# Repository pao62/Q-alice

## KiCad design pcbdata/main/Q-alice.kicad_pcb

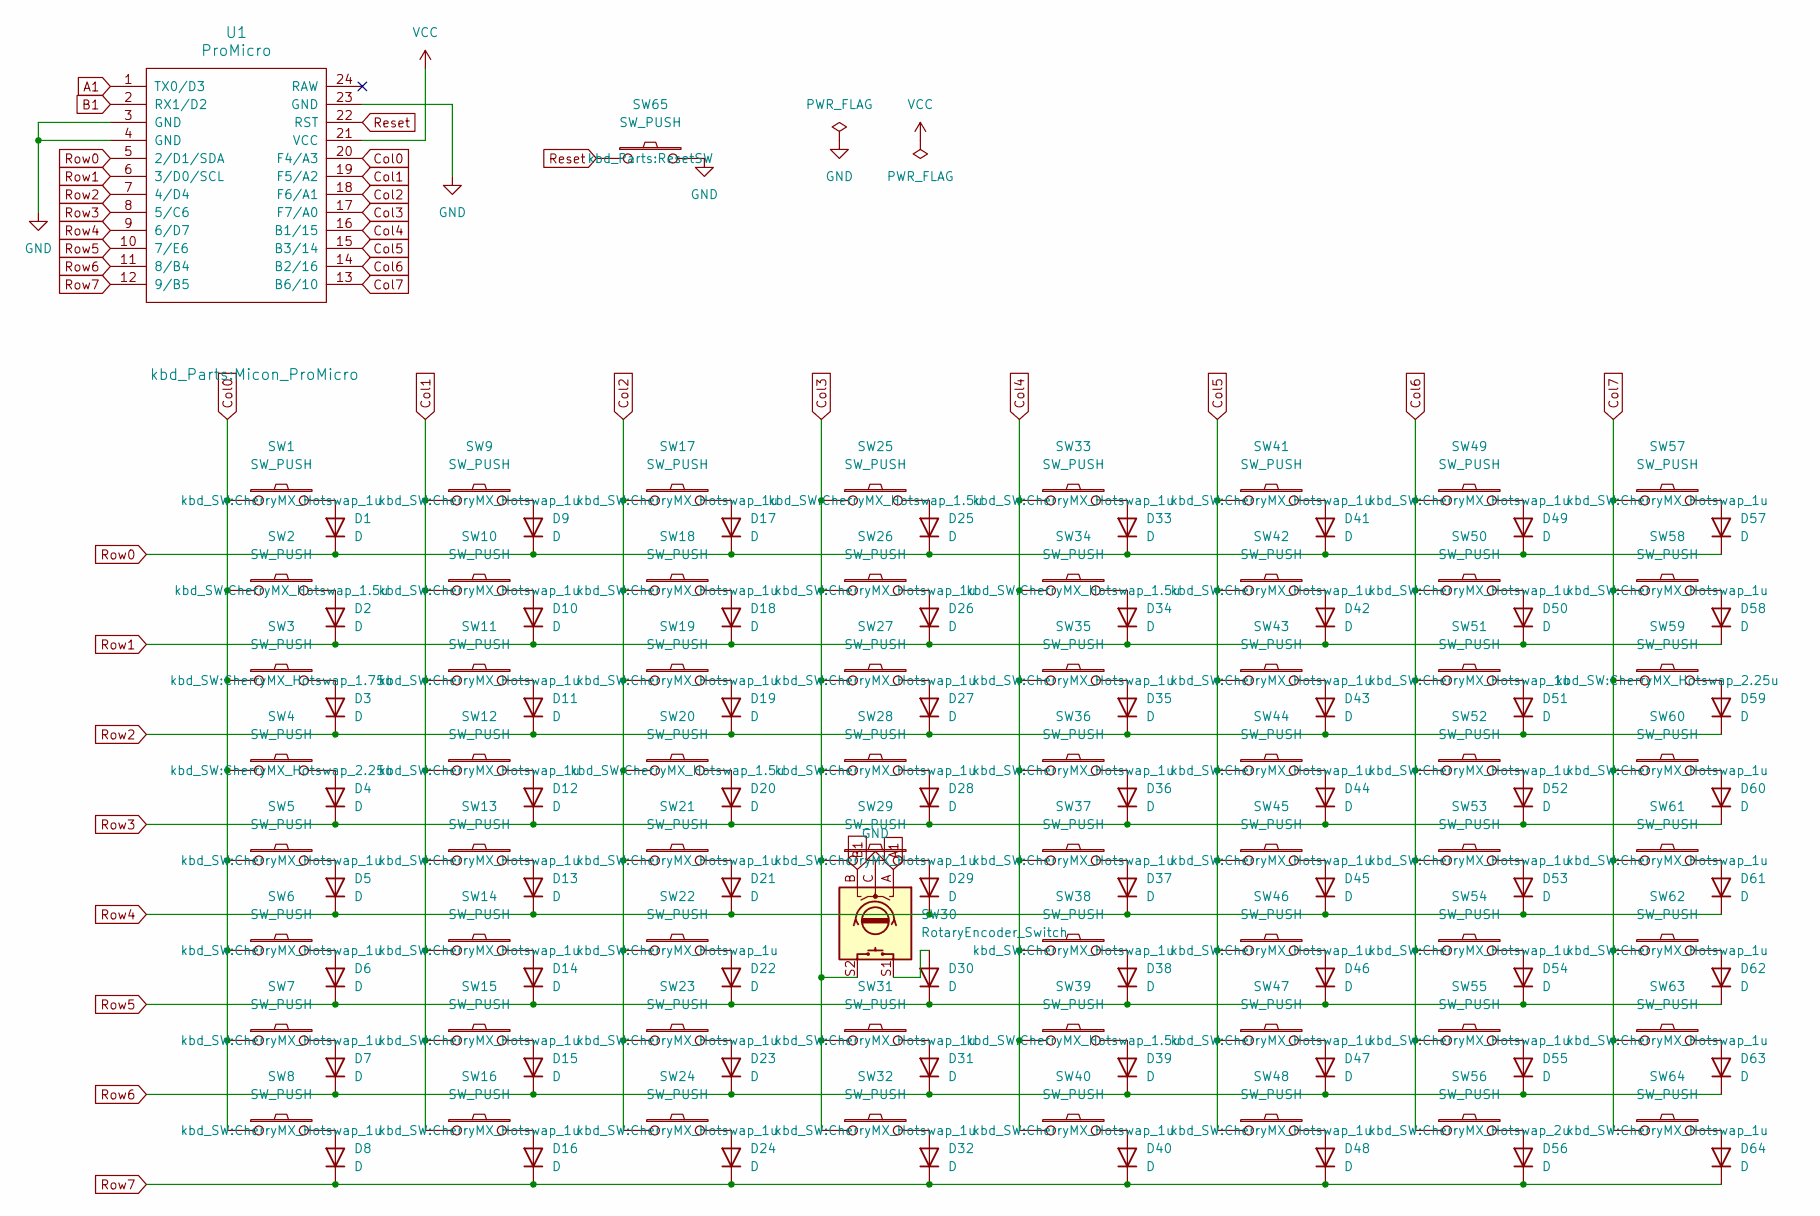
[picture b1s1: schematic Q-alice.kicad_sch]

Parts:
D1, D2, D3, D4, D5, D6, D7, D8, D9, D10, D11, D12, D13, D14, D15, D16, D17, D18, D19, D20, D21, D22, D23, D24, D25, D26, D27, D28, D29, D30, D31, D32, D33, D34, D35, D36, D37, D38, D39, D40, D41, D42, D43, D44, D45, D46, D47, D48, D49, D50, D51, D52, D53, D54, D55, D56, D57, D58, D59, D60, D61, D62, D63, D64: D; Diode_SMD
SW1, SW5, SW6, SW7, SW8, SW9, SW10, SW11, SW12, SW13, SW14, SW15, SW16, SW17, SW18, SW19, SW21, SW22, SW23, SW24, SW26, SW27, SW28, SW29, SW31, SW32, SW33, SW35, SW36, SW37, SW38, SW40, SW41, SW42, SW43, SW44, SW45, SW46, SW47, SW48, SW49, SW50, SW51, SW52, SW53, SW54, SW55, SW57, SW58, SW60, SW61, SW62, SW63, SW64: SW_PUSH; CherryMX_Hotswap_1u
SW2, SW20, SW25, SW34, SW39: SW_PUSH; CherryMX_Hotswap_1.5u
SW3: SW_PUSH; CherryMX_Hotswap_1.75u
SW4, SW59: SW_PUSH; CherryMX_Hotswap_2.25u
SW30: RotaryEncoder_Switch; RotaryEncoder_EC12E
SW56: SW_PUSH; CherryMX_Hotswap_2u
SW65: SW_PUSH; ResetSW
U1: ProMicro; Micon_ProMicro

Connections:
A1: SW30.A, U1.1 (TX0/D3)
B1: SW30.B, U1.2 (RX1/D2)
Col0: SW1.1, SW2.1, SW3.1, SW4.1, SW5.1, SW6.1, SW7.1, SW8.1, U1.20 (F4/A3)
Col1: SW9.1, SW10.1, SW11.1, SW12.1, SW13.1, SW14.1, SW15.1, SW16.1, U1.19 (F5/A2)
Col2: SW17.1, SW18.1, SW19.1, SW20.1, SW21.1, SW22.1, SW23.1, SW24.1, U1.18 (F6/A1)
Col3: SW25.1, SW26.1, SW27.1, SW28.1, SW29.1, SW30.S2, SW31.1, SW32.1, U1.17 (F7/A0)
Col4: SW33.1, SW34.1, SW35.1, SW36.1, SW37.1, SW38.1, SW39.1, SW40.1, U1.16 (B1/15)
Col5: SW41.1, SW42.1, SW43.1, SW44.1, SW45.1, SW46.1, SW47.1, SW48.1, U1.15 (B3/14)
Col6: SW49.1, SW50.1, SW51.1, SW52.1, SW53.1, SW54.1, SW55.1, SW56.1, U1.14 (B2/16)
Col7: SW57.1, SW58.1, SW59.1, SW60.1, SW61.1, SW62.1, SW63.1, SW64.1, U1.13 (B6/10)
GND: SW30.C, SW65.2, U1.3 (GND), U1.4 (GND), U1.23 (GND)
unnamed: D1.2 (A), SW1.2
unnamed: D2.2 (A), SW2.2
unnamed: D3.2 (A), SW3.2
unnamed: D4.2 (A), SW4.2
unnamed: D5.2 (A), SW5.2
unnamed: D6.2 (A), SW6.2
unnamed: D7.2 (A), SW7.2
unnamed: D8.2 (A), SW8.2
unnamed: D9.2 (A), SW9.2
unnamed: D10.2 (A), SW10.2
unnamed: D11.2 (A), SW11.2
unnamed: D12.2 (A), SW12.2
unnamed: D13.2 (A), SW13.2
unnamed: D14.2 (A), SW14.2
unnamed: D15.2 (A), SW15.2
unnamed: D16.2 (A), SW16.2
unnamed: D17.2 (A), SW17.2
unnamed: D18.2 (A), SW18.2
unnamed: D19.2 (A), SW19.2
unnamed: D20.2 (A), SW20.2
unnamed: D21.2 (A), SW21.2
unnamed: D22.2 (A), SW22.2
unnamed: D23.2 (A), SW23.2
unnamed: D24.2 (A), SW24.2
unnamed: D25.2 (A), SW25.2
unnamed: D26.2 (A), SW26.2
unnamed: D27.2 (A), SW27.2
unnamed: D28.2 (A), SW28.2
unnamed: D29.2 (A), SW29.2
unnamed: D30.2 (A), SW30.S1
unnamed: D31.2 (A), SW31.2
unnamed: D32.2 (A), SW32.2
unnamed: D33.2 (A), SW33.2
unnamed: D34.2 (A), SW34.2
unnamed: D35.2 (A), SW35.2
unnamed: D36.2 (A), SW36.2
unnamed: D37.2 (A), SW37.2
unnamed: D38.2 (A), SW38.2
unnamed: D39.2 (A), SW39.2
unnamed: D40.2 (A), SW40.2
unnamed: D41.2 (A), SW41.2
unnamed: D42.2 (A), SW42.2
unnamed: D43.2 (A), SW43.2
unnamed: D44.2 (A), SW44.2
unnamed: D45.2 (A), SW45.2
unnamed: D46.2 (A), SW46.2
unnamed: D47.2 (A), SW47.2
unnamed: D48.2 (A), SW48.2
unnamed: D49.2 (A), SW49.2
unnamed: D50.2 (A), SW50.2
unnamed: D51.2 (A), SW51.2
unnamed: D52.2 (A), SW52.2
unnamed: D53.2 (A), SW53.2
unnamed: D54.2 (A), SW54.2
unnamed: D55.2 (A), SW55.2
unnamed: D56.2 (A), SW56.2
unnamed: D57.2 (A), SW57.2
unnamed: D58.2 (A), SW58.2
unnamed: D59.2 (A), SW59.2
unnamed: D60.2 (A), SW60.2
unnamed: D61.2 (A), SW61.2
unnamed: D62.2 (A), SW62.2
unnamed: D63.2 (A), SW63.2
unnamed: D64.2 (A), SW64.2
Reset: SW65.1, U1.22 (RST)
Row0: D1.1 (K), D9.1 (K), D17.1 (K), D25.1 (K), D33.1 (K), D41.1 (K), D49.1 (K), D57.1 (K), U1.5 (2/D1/SDA)
Row1: D2.1 (K), D10.1 (K), D18.1 (K), D26.1 (K), D34.1 (K), D42.1 (K), D50.1 (K), D58.1 (K), U1.6 (3/D0/SCL)
Row2: D3.1 (K), D11.1 (K), D19.1 (K), D27.1 (K), D35.1 (K), D43.1 (K), D51.1 (K), D59.1 (K), U1.7 (4/D4)
Row3: D4.1 (K), D12.1 (K), D20.1 (K), D28.1 (K), D36.1 (K), D44.1 (K), D52.1 (K), D60.1 (K), U1.8 (5/C6)
Row4: D5.1 (K), D13.1 (K), D21.1 (K), D29.1 (K), D37.1 (K), D45.1 (K), D53.1 (K), D61.1 (K), U1.9 (6/D7)
Row5: D6.1 (K), D14.1 (K), D22.1 (K), D30.1 (K), D38.1 (K), D46.1 (K), D54.1 (K), D62.1 (K), U1.10 (7/E6)
Row6: D7.1 (K), D15.1 (K), D23.1 (K), D31.1 (K), D39.1 (K), D47.1 (K), D55.1 (K), D63.1 (K), U1.11 (8/B4)
Row7: D8.1 (K), D16.1 (K), D24.1 (K), D32.1 (K), D40.1 (K), D48.1 (K), D56.1 (K), D64.1 (K), U1.12 (9/B5)
VCC: U1.21 (VCC)

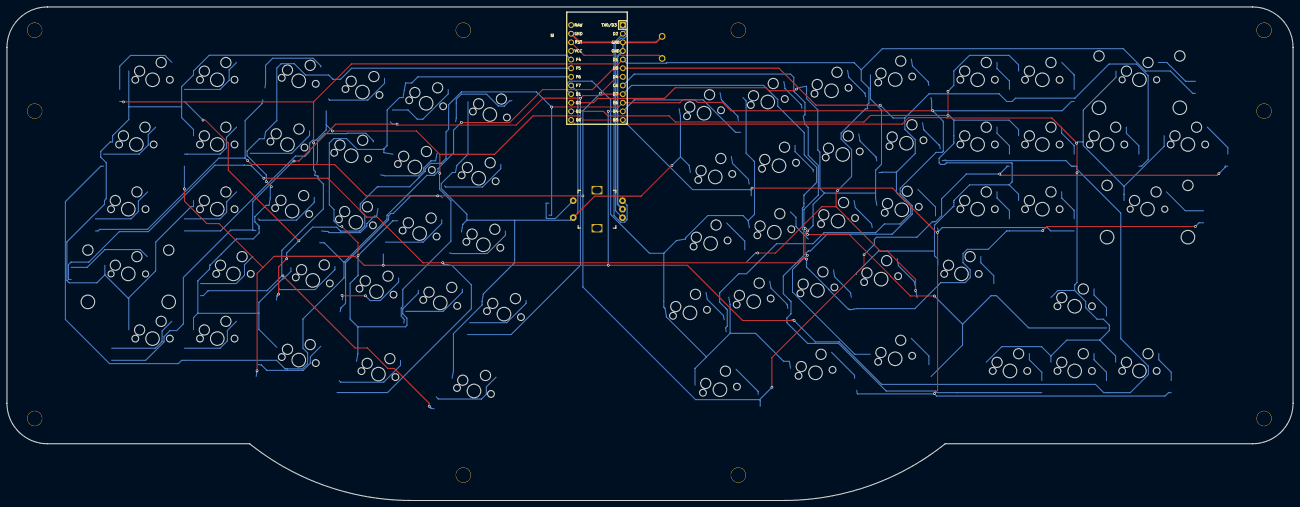
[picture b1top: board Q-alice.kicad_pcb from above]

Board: 2 copper layers, 378.6 x 145.3 mm, 140 parts (1 on the bottom side), 84 nets.

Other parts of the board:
Ref**: Val**; m2_Spacer_Hole
Ref**#2, Ref**#3, Ref**#4, Ref**#5, Ref**#6, Ref**#7, Ref**#8, Ref**#9, Ref**#10: Val**; m2_Spacer_Hole

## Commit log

2023-06-26 Create doc
